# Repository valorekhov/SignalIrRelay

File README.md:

SignalIrRelay
=============

ATMEGA328P-based 24 VAC to IR signal relay module. Designed for the use case of connecting 
a single-speed 24VAC thermostat fan output to a high-wall fan coil controlled via an IR remote.  

Features:

* Small board footprint 
* ICSP
* On-board TMP36 ambient temperature sensor and logic that controls fan speed given programmable dT
* Expansion port for the RF Link transmitter.

LICENSE:
Released under CERN Open Hardware License 1.1. See included license.txt file for details.

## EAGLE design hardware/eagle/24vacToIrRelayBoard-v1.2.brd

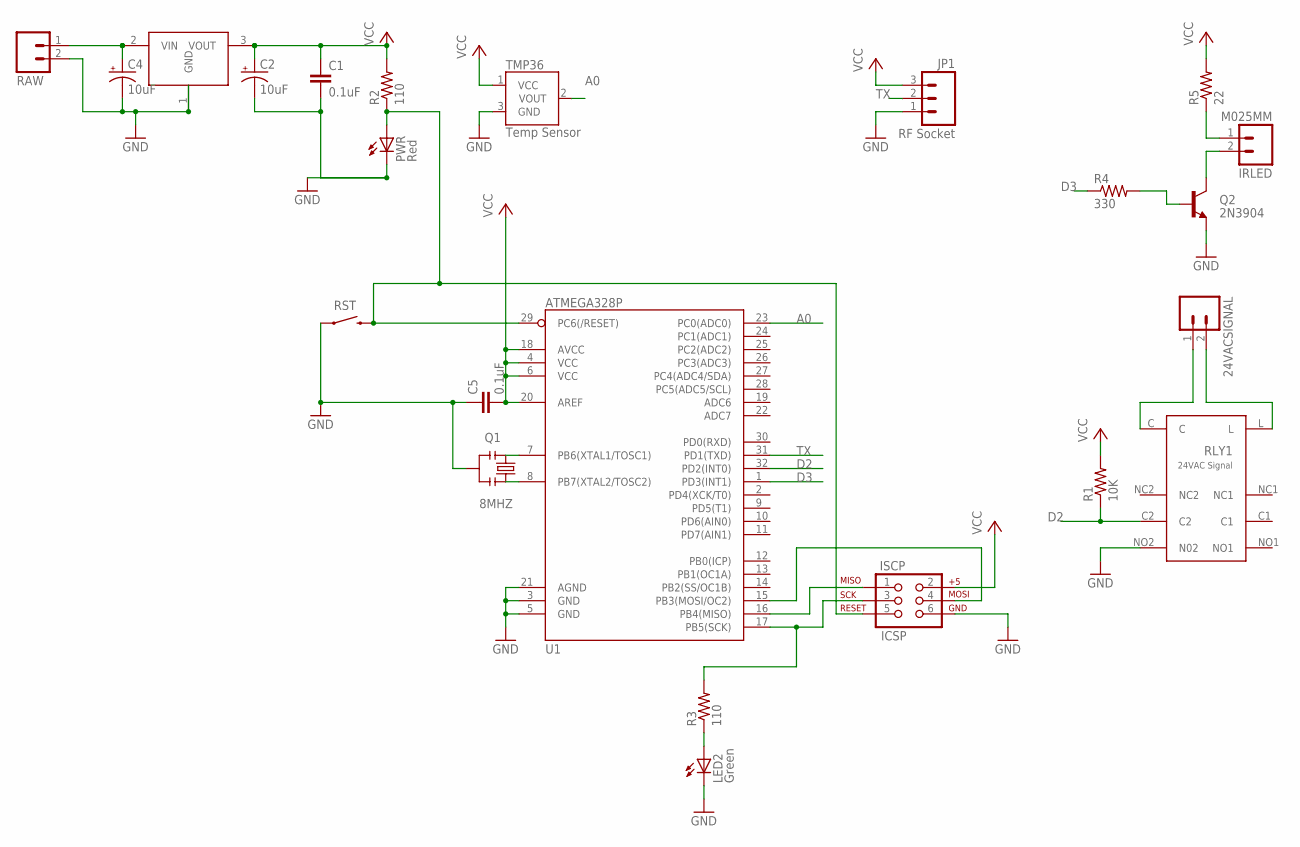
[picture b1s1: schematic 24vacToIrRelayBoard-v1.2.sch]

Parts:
24VACSIGNAL: M025MM; SCREWTERMINAL-5MM-2
C1, C5: 0.1uF; 0603-CAP
C2, C4: 10uF; EIA3216
IRLED: M025MM; SCREWTERMINAL-5MM-2
ISCP: ICSP; 2X3-NS
JP1: RF Socket; 1X03
LED2: Green; LED-0603
PWR: Red; LED-0603
Q1: 8MHZ; RESONATOR-SMD
Q2: 2N3904; SOT23-3
R1: 10K; 0603-RES
R2, R3: 110; 0603-RES
R4: 330; 0603-RES
R5: 22; 0603-RES
RAW: M025MM; SCREWTERMINAL-5MM-2
RLY1: 24VAC Signal; 976RELAY
RST: SWITCH-MOMENTARY-2PTH; TACTILE-PTH
TMP36: Temp Sensor; TO-92
U1: ATMEGA328P; TQFP32-08
U$1: MCP1702; TO92

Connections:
A0: TMP36.2 (VOUT), U1.23 (PC0(ADC0))
D2: R1.1, RLY1.C2, U1.32 (PD2(INT0))
D3: R4.1, U1.1 (PD3(INT1))
GND: C1.2, C2.C (-), C4.C (-), C5.1, ISCP.6, JP1.1, LED2.C, PWR.C, Q1.2, Q2.2 (E), RAW.2, RLY1.NO2 (N02), RST.1, TMP36.3 (GND), U1.3 (GND), U1.5 (GND), U1.21 (AGND), U$1.1 (GND)
MISO: ISCP.1, U1.16 (PB4(MISO))
MOSI: ISCP.4, U1.15 (PB3(MOSI/OC2))
unnamed: C4.A (+), RAW.1, U$1.2 (VIN)
unnamed: Q1.1, U1.7 (PB6(XTAL1/TOSC1))
unnamed: Q1.3, U1.8 (PB7(XTAL2/TOSC2))
unnamed: LED2.A, R3.1
unnamed: IRLED.1, R5.1
unnamed: IRLED.2, Q2.3 (C)
unnamed: Q2.1 (B), R4.2
unnamed: 24VACSIGNAL.2, RLY1.L
unnamed: 24VACSIGNAL.1, RLY1.C
RST: ISCP.5, PWR.A, R2.1, RST.3 (2), U1.29 (PC6(/RESET))
SCK: ISCP.3, R3.2, U1.17 (PB5(SCK))
TX: JP1.2, U1.31 (PD1(TXD))
VCC: C1.1, C2.A (+), C5.2, ISCP.2, JP1.3, R1.2, R2.2, R5.2, TMP36.1 (VCC), U1.4 (VCC), U1.6 (VCC), U1.18 (AVCC), U1.20 (AREF), U$1.3 (VOUT)

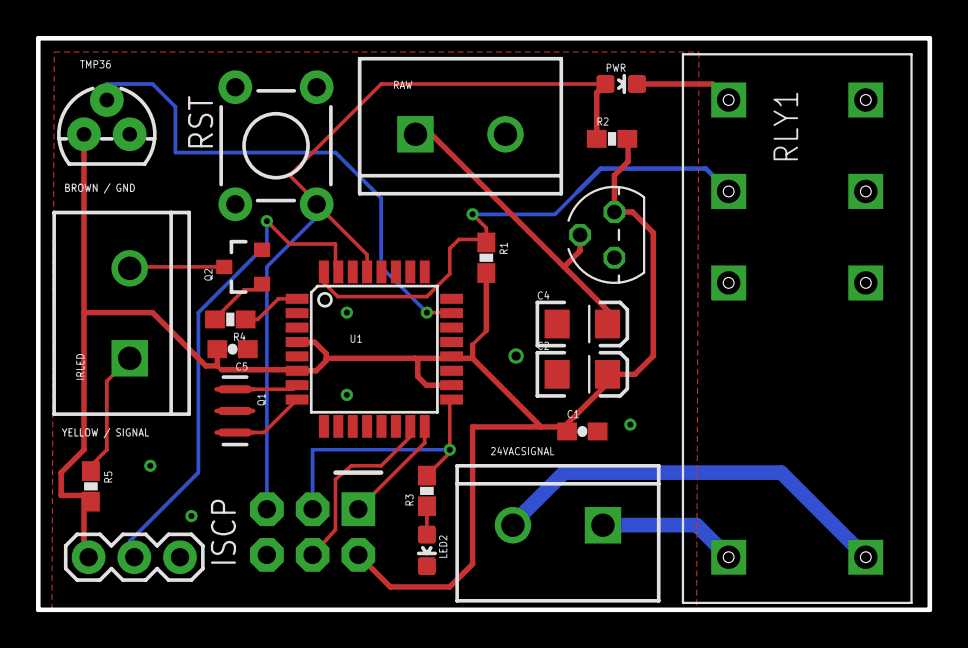
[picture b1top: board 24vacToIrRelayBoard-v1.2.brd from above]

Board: 2 copper layers, 49.6 x 31.8 mm, 23 parts (0 on the bottom side), 19 nets.

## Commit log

2014-06-28 Add datasheets
2014-06-28 ADD CERN OSH License
2014-06-28 Mod readme
2014-07-04 tweaks to dT settings, ramp up, ramp down behaviours added
2016-07-30 Increase temp thresholds to favour lower fan speeds for better degumidification
2016-08-03 Update Low, Med sequences to use High louver position, add capture script
2022-06-05 Migrate to PlatformIO project
2022-06-30 Platformio fixes; change rampdown

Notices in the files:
parts and their libraries:
SparkFun-Electromechanical: Licensing: Creative Commons ShareAlike 4.0 International - https://creativecommons.org/licenses/by-sa/4.0
